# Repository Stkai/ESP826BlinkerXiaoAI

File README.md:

# ESP826BlinkerXiaoai
小爱同学控制舵机实现开关灯

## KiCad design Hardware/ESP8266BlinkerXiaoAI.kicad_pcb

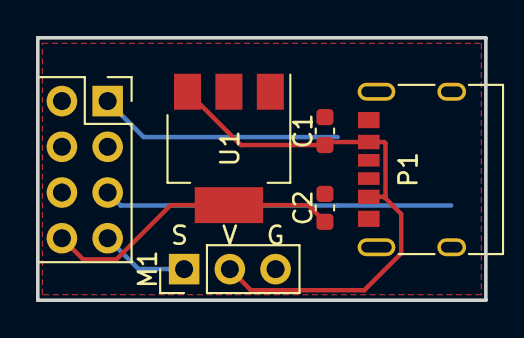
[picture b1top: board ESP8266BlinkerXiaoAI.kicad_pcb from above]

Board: 2 copper layers, 24.9 x 14.6 mm, 7 parts (1 on the bottom side), 5 nets.

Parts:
C1, C2: C; C_0603_1608Metric
J1: Conn_02x04_Top_Bottom; PinSocket_2x04_P2.54mm_Vertical
M1: Motor_Servo; PinHeader_1x03_P2.54mm_Vertical
P1: USB_C_Plug_USB2.0; USB_C_6P
SW1: SW_Push; SW_SPST_TL3342
U1: AMS1117; SOT-223-3_TabPin2

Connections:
+3V3: C2.1, J1.8, U1.2 (VO)
+5V: C1.1, M1.2 (+), P1.A9 (VBUS), P1.B9 (VBUS), U1.3 (VI)
/IO0: J1.5, SW1.1
/RX: J1.7, M1.1 (PWM)
GND: C1.2, C2.2, J1.1, M1.3 (-), P1.A12 (GND), P1.B12 (GND), SW1.2, U1.1 (ADJ)

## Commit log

2022-02-26 ESP8266 接入小爱同学控制开关灯
2022-03-07 V1.1
2022-03-08 V1.2
2022-03-10 PlatformIO version
